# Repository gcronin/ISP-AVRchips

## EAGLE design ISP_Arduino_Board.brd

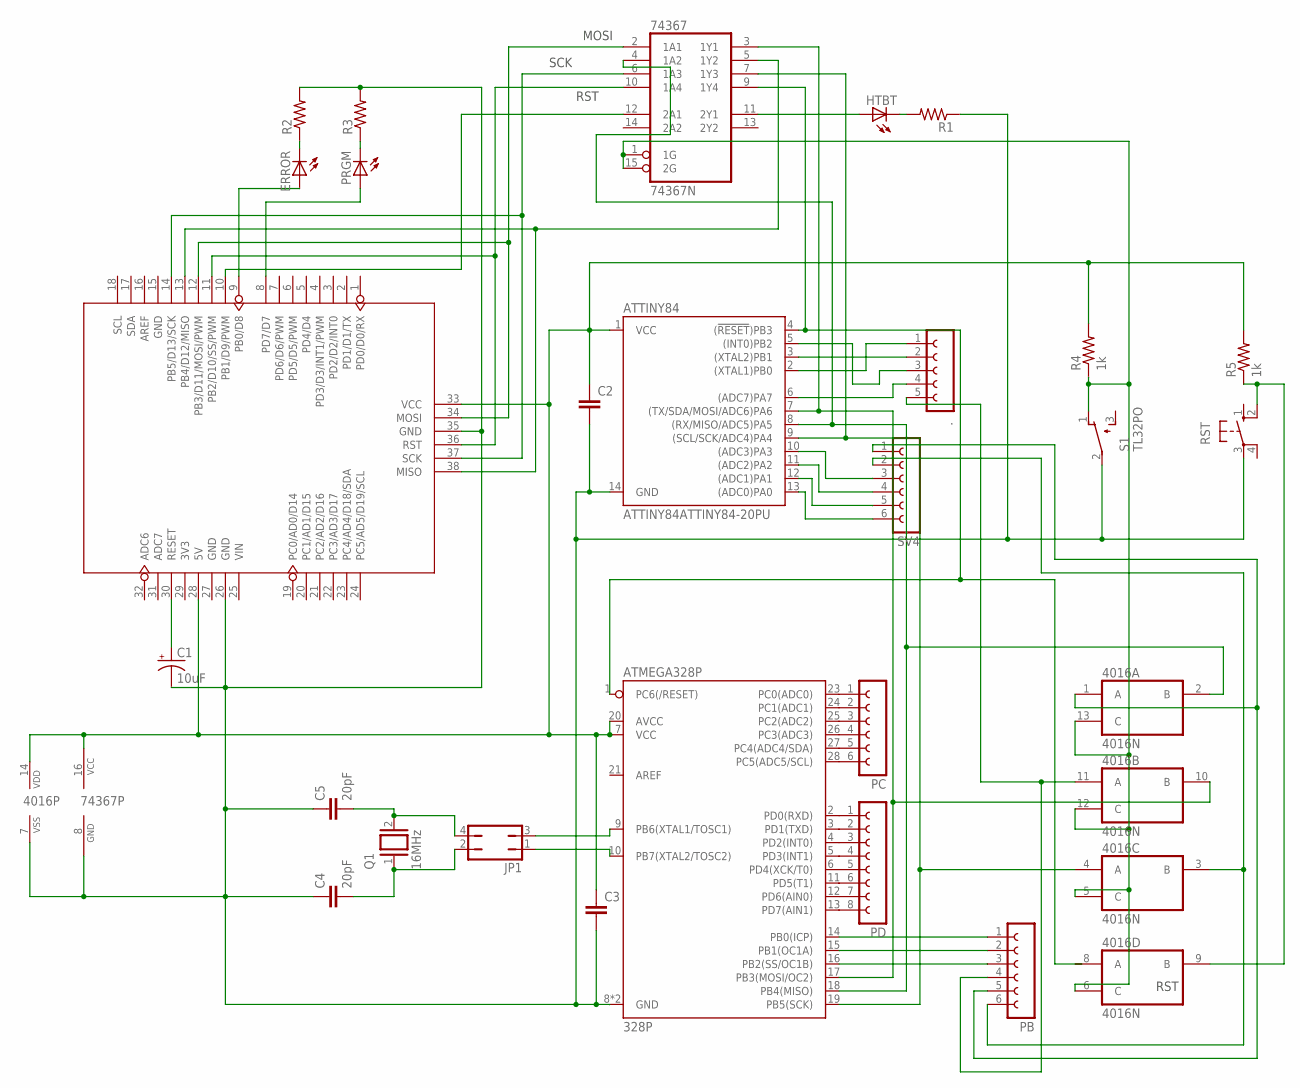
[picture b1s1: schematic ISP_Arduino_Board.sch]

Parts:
4016: 4016N; DIL14
74367: 74367N; DIL16
.: FE05-1
ATMEGA328P: 328P; DIP28
ATTINY84: ATTINY84ATTINY84-20PU; DIP14
C1: 10uF; E2,5-6
C2, C3: C2,5-3; C2.5-3
C4, C5: 20pF; C2.5-3
ERROR: LED3MM
HTBT: LED3MM
JP1: JP2Q
PB: FE06-1; FE06
PC: FE06-1; FE06
PD: FE08-1; FE08
PRGM: LED3MM
Q1: 16MHz; QS
R1, R2, R3: R-US_0207/10; 0207/10
R4, R5: 1k; 0207/10
RST: 10-XX; B3F-10XX
S1: TL32PO; TL3XPO
SV4: FE06-1; FE06
U2: DIP Long Blue Female Header; ARDUINO-38P

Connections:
GND: 4016.7 (VSS), 74367.8 (GND), ATMEGA328P.8 (GND), ATMEGA328P.22 (GND), ATTINY84.14 (GND), C1.-, C2.2, C3.2, C4.1, C5.1, R1.1, R2.2, R3.2, RST.3, S1.2, U2.26 (GND), U2.35 (GND)
unnamed: 4016.14 (VDD), 74367.16 (VCC), ATMEGA328P.7 (VCC), ATMEGA328P.20 (AVCC), ATTINY84.1 (VCC), C2.1, C3.1, R4.2, R5.2, U2.28 (5V), U2.33 (VCC)
unnamed: 4016.11 (A), ..5, PB.4
unnamed: 4016.4 (A), 74367.7 (1Y3), ATMEGA328P.19 (PB5(SCK)), ATTINY84.9 ((SCL/SCK/ADC4)PA4)
unnamed: C1.+, U2.30 (RESET)
unnamed: 4016.2 (B), 74367.4 (1A2), ATMEGA328P.18 (PB4(MISO)), ATTINY84.8 ((RX/MISO/ADC5)PA5)
unnamed: ATMEGA328P.14 (PB0(ICP)), PB.1
unnamed: PRGM.K (C), R3.1
unnamed: C5.2, JP1.4, Q1.2
unnamed: ERROR.K (C), R2.1
unnamed: HTBT.K (C), R1.2
unnamed: 74367.12 (2A1), U2.10 (PB1/D9/PWM)
unnamed: 74367.2 (1A1), U2.12 (PB3/D11/MOSI/PWM), U2.34 (MOSI)
unnamed: PRGM.A, U2.8 (PD7/D7)
unnamed: 74367.9 (1Y4), ATMEGA328P.1 (PC6(/RESET)), ATTINY84.4 ((!RESET!)PB3)
unnamed: C4.2, JP1.2, Q1.1
unnamed: ATMEGA328P.9 (PB6(XTAL1/TOSC1)), JP1.3
unnamed: ATMEGA328P.10 (PB7(XTAL2/TOSC2)), JP1.1
unnamed: ERROR.A, U2.9 (PB0/D8)
unnamed: 74367.10 (1A4), U2.11 (PB2/D10/SS/PWM), U2.36 (RST)
unnamed: 74367.5 (1Y2), U2.13 (PB4/D12/MISO), U2.38 (MISO)
unnamed: 74367.6 (1A3), U2.14 (PB5/D13/SCK), U2.37 (SCK)
unnamed: ATMEGA328P.2 (PD0(RXD)), PD.1
unnamed: ATMEGA328P.3 (PD1(TXD)), PD.2
unnamed: 4016.5 (C), 4016.6 (C), 4016.12 (C), 4016.13 (C), 74367.1 (1G), 74367.15 (2G), R4.1, S1.1 (O)
unnamed: ATMEGA328P.23 (PC0(ADC0)), PC.1
unnamed: ATMEGA328P.24 (PC1(ADC1)), PC.2
unnamed: ATMEGA328P.25 (PC2(ADC2)), PC.3
unnamed: ATMEGA328P.26 (PC3(ADC3)), PC.4
unnamed: ATMEGA328P.27 (PC4(ADC4/SDA)), PC.5
unnamed: ATMEGA328P.28 (PC5(ADC5/SCL)), PC.6
unnamed: ATMEGA328P.4 (PD2(INT0)), PD.3
unnamed: ATMEGA328P.5 (PD3(INT1)), PD.4
unnamed: ATMEGA328P.6 (PD4(XCK/T0)), PD.5
unnamed: ATMEGA328P.11 (PD5(T1)), PD.6
unnamed: ATMEGA328P.12 (PD6(AIN0)), PD.7
unnamed: ATMEGA328P.13 (PD7(AIN1)), PD.8
unnamed: ATMEGA328P.15 (PB1(OC1A)), PB.2
unnamed: ATMEGA328P.16 (PB2(SS/OC1B)), PB.3
unnamed: 4016.3 (B), PB.6, SV4.2
unnamed: 4016.1 (A), PB.5, SV4.1
unnamed: 4016.9 (B), R5.1, RST.2 (S1)
unnamed: 74367.11 (2Y1), HTBT.A
unnamed: ..1, ATTINY84.2 ((XTAL1)PB0)
unnamed: ..2, ATTINY84.3 ((XTAL2)PB1)
unnamed: ..3, ATTINY84.5 ((INT0)PB2)
unnamed: ..4, ATTINY84.6 ((ADC7)PA7)
unnamed: ATTINY84.13 ((ADC0)PA0), SV4.6
unnamed: ATTINY84.12 ((ADC1)PA1), SV4.5
unnamed: ATTINY84.11 ((ADC2)PA2), SV4.4
unnamed: ATTINY84.10 ((ADC3)PA3), SV4.3
PD: 4016.10 (B), 74367.3 (1Y1), ATMEGA328P.17 (PB3(MOSI/OC2)), ATTINY84.7 ((TX/SDA/MOSI/ADC6)PA6)

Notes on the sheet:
SCK
MOSI
RST

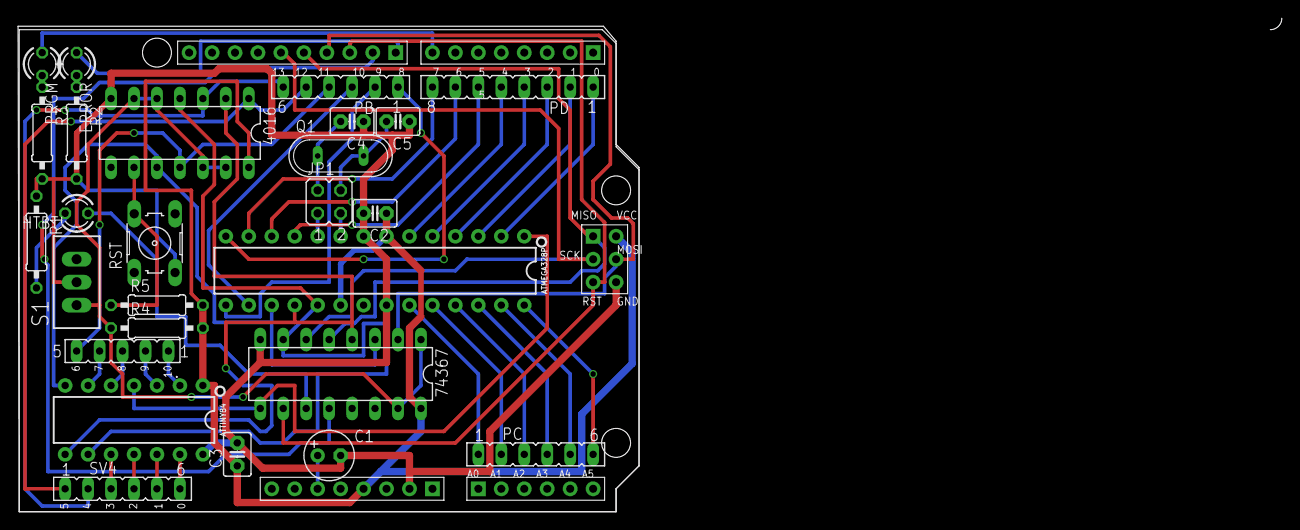
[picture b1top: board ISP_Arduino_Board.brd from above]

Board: 2 copper layers, 139.8 x 54.6 mm, 27 parts (0 on the bottom side), 52 nets.

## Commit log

2022-03-14 Eagle Files & Pin Test Sketch

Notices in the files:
parts and their libraries:
SparkFun-IC-Microcontroller: Licensing: Creative Commons ShareAlike 4.0 International - https://creativecommons.org/licenses/by-sa/4.0
